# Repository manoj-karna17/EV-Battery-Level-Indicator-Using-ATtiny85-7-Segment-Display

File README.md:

=================================================================================================================
                                      EV-Battery-Level-Indicator-Using-ATtiny85-7-Segment-Display
           =================================================================================================================
----------------------
Project Description:
----------------------
This project monitors and displays the voltage level of an electric vehicle (EV) battery using a 
microcontroller-based setup.The  system uses analog voltage sampling, voltage regulation,
and a 74HC595 shift register to drive a 7-segment LED display, all  designed and tested using KiCad.

---------------
Components:
---------------
1. ATtiny85 microcontroller
2. LM7805 Voltage Regulator
3. 74HC595 Shift Register
4. 7-Segment LED Display
5. Voltage Divider Circuit
6. 12V Battery
7. Resistors

---------------
Tools Used:
---------------
KiCad (Schematic, PCB, Gerber, BOM)

-----------------
Pin Connections:
-----------------
ATtiny85 → 74HC595
-----------------------------------------------------------------------
ATtiny85 Pin	|         Function	    |       74HC595 Pin    |
-----------------------------------------------------------------------
PB1 (Pin 6)	|         Data (MOSI)	    |       DS (Pin 14)    |
-----------------------------------------------------------------------
PB2 (Pin 7)	|         Clock (SCK)	    |       SH_CP (Pin 11) |
-----------------------------------------------------------------------
PB0 (Pin 5)	|         Latch	    |       ST_CP (Pin 12) |
-----------------------------------------------------------------------

1. ATtiny85 PB3 (Pin 2) → Voltage divider output (Analog input).
2. 74HC595 Q0-Q6 → 7-Segment Display segments (with resistors).
3. Common pin of 7-Segment → VCC (Common Anode) or GND (Common Cathode).
4All grounds connected together.
----------------
How it works:
----------------
12Volts Battery
      |
      v
Voltage Regulator (LM7805): Converts 12V to 5V
      |
      v
Voltage Divider: Scales the battery voltage
      |
      v
Micro controller (ATtiny85): Reads voltage and calculates battery level
      |
      v
Shift register (74HC595): Send data to display
      |
      v
7-Segment display: Shows battery level

---------------
Step Process:
---------------
1. Power Supply – The circuit is powered from the EV’s 12V battery.
2. Voltage Regulation – LM7805 converts 12V down to a stable 5V for all components.
3. Voltage Sensing – A resistor divider scales the battery voltage for safe measurement.
4. Voltage Measurement – ATtiny85 reads voltage via ADC.
5. Battery Level Calculation – The microcontroller maps voltage to battery percentage/level.
6. Data Output – Battery level is sent to 74HC595 shift register.
7. Display – The 7-segment display shows the calculated battery level.
------------
Notes:
------------
1. Adjust voltage divider resistor values according to your battery voltage range.
2. Always use resistors for each display segment to prevent damage.

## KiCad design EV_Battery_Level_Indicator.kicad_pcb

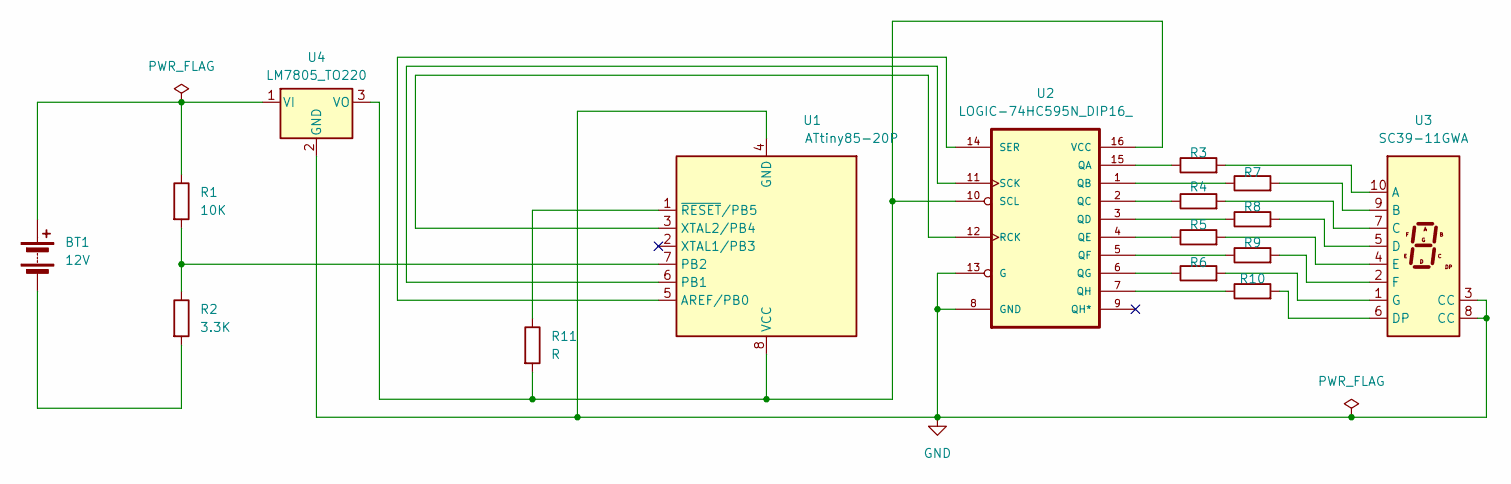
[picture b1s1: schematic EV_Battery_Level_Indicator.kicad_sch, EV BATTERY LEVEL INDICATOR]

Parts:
BT1: 12V
R1: 10K; R_Axial_DIN0207_L6.3mm_D2.5mm_P7.62mm_Horizontal
R2: 3.3K; R_Axial_DIN0207_L6.3mm_D2.5mm_P7.62mm_Horizontal
R3, R4, R5, R6, R7, R8, R9, R10: 220; R_Axial_DIN0207_L6.3mm_D2.5mm_P7.62mm_Horizontal
R11: R; R_Axial_DIN0204_L3.6mm_D1.6mm_P7.62mm_Horizontal
U1: ATtiny85-20P; DIP-8_W7.62mm
U2: LOGIC-74HC595N_DIP16_; DIP16-2.54-20.32X5.84MM; MPN 74HC595N
U3: SC39-11GWA; Sx39-1xxxxx
U4: LM7805_TO220; TO-220-3_Vertical

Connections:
GND: U1.4 (GND), U2.8 (GND), U2.13 (G), U3.3 (CC), U3.8 (CC), U4.2 (GND)
unnamed: BT1.1 (+), R1.1, U4.1 (VI)
unnamed: BT1.2 (-), R2.2
unnamed: U1.5 (AREF/PB0), U2.14 (SER)
unnamed: U1.6 (PB1), U2.11 (SCK)
unnamed: R1.2, R2.1, U1.7 (PB2)
unnamed: R11.2, U1.8 (VCC), U2.10 (SCL), U2.16 (VCC), U4.3 (VO)
unnamed: U1.3 (XTAL2/PB4), U2.12 (RCK)
unnamed: R11.1, U1.1 (~RESET/PB5)
unnamed: R3.1, U2.15 (QA)
unnamed: R7.1, U2.1 (QB)
unnamed: R4.1, U2.2 (QC)
unnamed: R8.1, U2.3 (QD)
unnamed: R5.1, U2.4 (QE)
unnamed: R9.1, U2.5 (QF)
unnamed: R6.1, U2.6 (QG)
unnamed: R10.1, U2.7 (QH)
unnamed: R3.2, U3.10 (A)
unnamed: R7.2, U3.9 (B)
unnamed: R4.2, U3.7 (C)
unnamed: R8.2, U3.5 (D)
unnamed: R10.2, U3.6 (DP)
unnamed: R5.2, U3.4 (E)
unnamed: R9.2, U3.2 (F)
unnamed: R6.2, U3.1 (G)

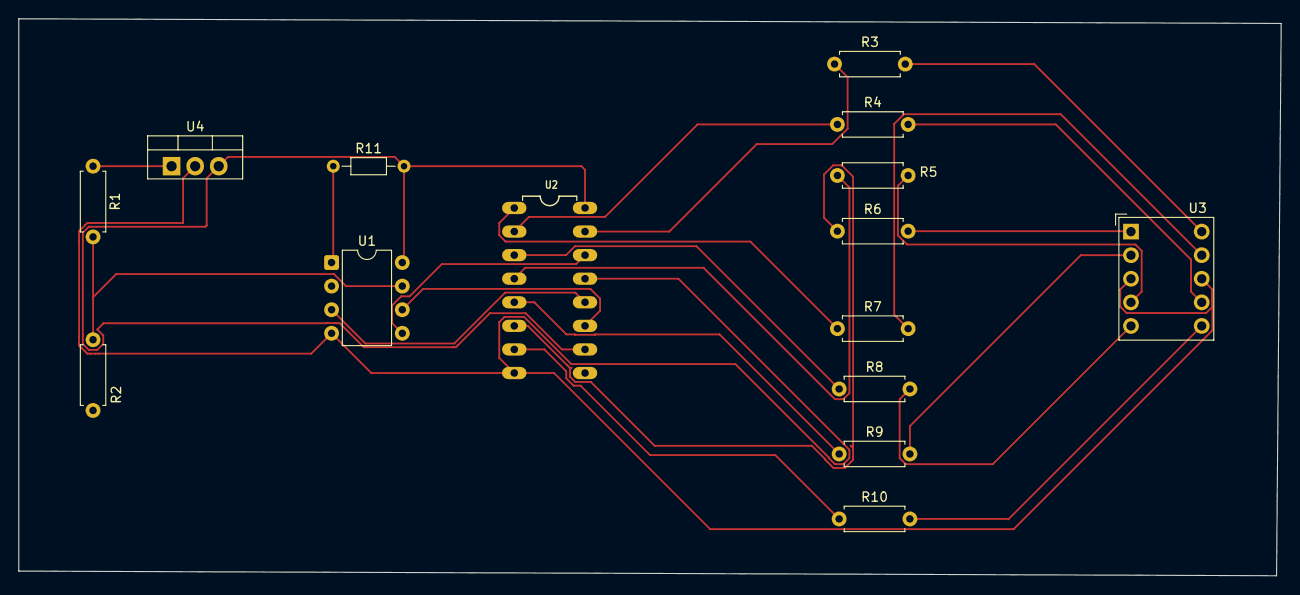
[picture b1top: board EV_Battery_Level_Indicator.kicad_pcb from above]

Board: 2 copper layers, 136.0 x 60.0 mm, 15 parts (0 on the bottom side), 24 nets.
